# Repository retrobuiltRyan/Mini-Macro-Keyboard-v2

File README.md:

# Mini-Macro-Keyboard-v2
 A macro keyboard to improve application workflow by hardcoding macros, hotkeys, and shortcuts in a tiny keyboard. There is a mode button + OLED screen breakout that allows the user to add multiple macro profiles. A focus on backwards compatibility utilizing cheaper components and versatility was key so many USB input devices can be made cheaply. You can populate the board with a mix of rotary encoders, Cherry keys, or tactile switches. This keyboard was a built for hot-key Retropie commands in Raspberry Pi arcades.This PCB can be populated with up to 5 Cherry Mx Keys and 1 rotary encoders (or omit the encoders for 6 keys). An additional 2 key breakout board can be used (with a TRS cable) to locate 2 cherry keys in discrete location (like a foot pedal). 
In action here: https://youtu.be/HfOvEncG98M?t=264

Suggested Parts List:

| Qty | Description | DigiKey P/N| Notes |
| -------- | --------|--------| ---------------- |
| 1 | Arduino Pro Micro|ebay is cheaper| |
| 6| Cherry Mx Switch |CH196-ND| Or any cherry compatible switch. RGB type are recommended |
| 6| CHERRY MX KEYCAP |1568-PRT-15306-ND |Clear keycap is recommended|
|1|Rotary Encoder w/ Switch |987-1398-ND|Solder encoder jumpers to enable signal paths |
|1|Knob for Rotary shaft, 6mm dia |n/a just get it from ebay|optional|
|1|DIP PCB Mount 5 Pins 3.5mm Socket Headphone Stereo Audio Jack |CP1-3524NG-ND|optional|
|1|Resistor 330 OHM 1206 |RMCF1206JT330RCT-ND|for Addressable LED Data-in line|
|7|SK6812 MINI-E Addressable RGB LED 5V 3228 SMD |[Aliexpress](https://www.aliexpress.us/item/2255800289371100.html?spm=a2g0s.12269583.0.0.572c1e9ceHD99V&gatewayAdapt=glo2usa4itemAdapt&_randl_shipto=US)|solder "LED PWR" jumper if using addressable LEDs|
|1|SWITCH TACTILE SPST-NO 0.05A 12V (6x6mm) |679-2443-ND||
|2|1x12 Header 0.1" pitch|S6100-ND||
|8|Diode *(OPTIONAL)*, small signal, SOD-123 |1N4148W-13FDICT-ND|Solder Diode bypass jumpers if not using diodes. Diodes are optional|

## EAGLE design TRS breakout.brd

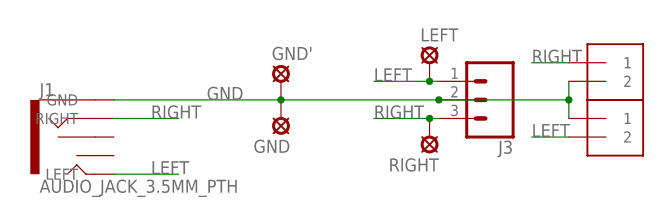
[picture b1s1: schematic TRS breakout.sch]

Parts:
GND: SE14
GND': SE14
J1: AUDIO_JACK_3.5MM_PTH; AUDIO-JACK
J3: CONN_03LOCK_LONGPADS; 1X03_LOCK_LONGPADS
J4, J5: 1X2-3.5MM
LEFT: SE14
RIGHT: SE14

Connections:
GND: GND.MP, GND'.MP, J1.GND, J3.2, J4.1, J5.2
LEFT: J1.LEFT, J3.1, J4.2, LEFT.MP
RIGHT: J1.RIGHT, J3.3, J5.1, RIGHT.MP

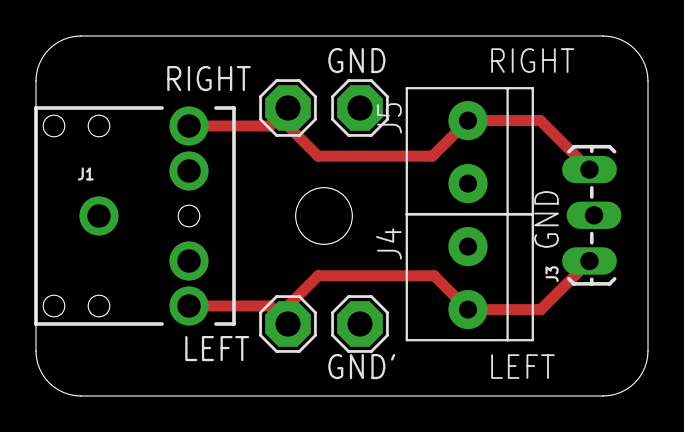
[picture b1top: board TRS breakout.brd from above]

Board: 2 copper layers, 34.0 x 20.0 mm, 8 parts (0 on the bottom side), 3 nets.

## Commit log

2022-12-23 Example code for Retropie Auto attract mode.
    Best for 8-16 bit emulators in Retropie.
    Mode 0 (default) is hotkey shortcuts for Retropie. Keys like Load state, Save State, Reset, + Quit are bound and displayed on the OLED (if attached).
    Mode 1 enables an auto demo then Quit-game based on the potentiometer setting. Will let a game run from 30s to 10min, quit, then select the next on in the emulator list. Makes for cool arcade attract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
2022-12-23 Schematic and PCB layout for reference
2022-12-23 3D Print Case, Design Files
2022-12-23 Laser Cut Design Files
    Edit/ open with Inkscape!
2022-12-23 TRS 2-Key Auxiliary PCB Design Files
    The main macro keyboard is a 2x4 row column matrix (see schematic). Keys #4 and #8 are accessible via the TRS jack (3.5mm audio cable). These are the design files for the auxiliary board.
    Designed in Eagle CAD 9.x

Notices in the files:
parts and their libraries:
SparkFun-Connectors: Licensing: Creative Commons ShareAlike 4.0 International - https://creativecommons.org/licenses/by-sa/4.0
